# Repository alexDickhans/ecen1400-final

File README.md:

# ECEN 1400 Final Project: Interactive Multi-Game Board System

A physical implementation of multiple board games (Gomoku and Connect 4) using Arduino microcontrollers and servo motors, featuring dual input controllers with haptic feedback and game mode selection.

## 📄 [Project Final Report](/final-report.pdf)

## 🎮 Project Overview

This project creates an interactive 5x5 game board system that supports multiple game modes. Players use physical controllers to place X and O pieces represented by servo motor positions. The system includes haptic feedback, game mode selection, and supports two different input methods (button-based and joystick-based controllers).

## 🏗️ System Architecture

The system consists of three main components:

### 1. Main Board Controller (`main-board/`)
- **Hardware**: Arduino Uno with 2x PCA9685 PWM Servo Driver boards
- **Function**: Controls 25 servo motors arranged in a 5x5 grid
- **Features**: 
  - Multiple game modes (Gomoku 3-5 in a row, Connect 4 3-5 in a row)
  - Game mode selection with visual feedback
  - Game logic and win detection
  - Cursor animation and visual feedback
  - Dual controller communication (separate X and O player controllers)
  - Win sequence animations
  - On-board button controls (SELECT and RESET/START)
  - Movement queue system for optimized servo control

### 2. Coarse Input Controller (`coarse/`)
- **Hardware**: Arduino Uno with 5 digital buttons
- **Function**: Provides directional input via discrete buttons (typically used as one player controller)
- **Features**:
  - Up/Down/Left/Right/Select button inputs
  - Dual UART communication (Hardware Serial + SoftwareSerial)
  - Haptic feedback motor control with multiple patterns

### 3. Fine Input Controller (`fine/`)
- **Hardware**: Arduino Uno with analog joystick
- **Function**: Provides directional input via joystick (typically used as the other player controller)
- **Features**:
  - Analog joystick with threshold detection
  - Dual UART communication (Hardware Serial + SoftwareSerial)
  - Haptic feedback motor control with multiple patterns

## 🔌 Pin Configurations

### Main Board Controller
- **PCA9685 Board 1** (Address 0x40, A0 bridged): Controls servos 0-14
- **PCA9685 Board 2** (Address 0x60, all address pins grounded): Controls servos 15-24
- **X Player Controller**: AltSoftSerial on pins 8/9 (RX/TX)
- **O Player Controller**: SoftwareSerial on pins 5/6 (RX/TX)
- **SELECT Button**: Pin 7 (INPUT_PULLUP)
- **RESET/START Button**: Pin 8 (INPUT_PULLUP) - Note: conflicts with AltSoftSerial, consider different pin

### Coarse Controller
- **Buttons**: 
  - Up: Pin 8
  - Down: Pin 9
  - Left: Pin 10
  - Right: Pin 11
  - Select: Pin 12
- **Haptic Motor**: Pin 13
- **UART**: Hardware Serial (0/1) + SoftwareSerial (4/5 - RX/TX)

### Fine Controller
- **Joystick X**: Pin A0
- **Joystick Y**: Pin A1
- **Select Button**: Pin 3 (INPUT_PULLUP)
- **Haptic Motor**: Pin 13
- **UART**: Hardware Serial (0/1) + SoftwareSerial (6/7 - RX/TX)

## 🎯 Game Features

### Game Modes
The system supports 6 different game modes:

**Gomoku Modes (0-2):**
- Mode 0: 3 in a row (tic-tac-toe style, uses 3x3 sub-board)
- Mode 1: 4 in a row
- Mode 2: 5 in a row (classic Gomoku)

**Connect 4 Modes (3-5):**
- Mode 3: Connect 3
- Mode 4: Connect 4 (classic)
- Mode 5: Connect 5

### Servo States
- **STATE_NONE** (Position 300): Empty space
- **STATE_X** (Position 470): Player X piece
- **STATE_O** (Position 100): Player O piece

### Game Mechanics
- **5x5 Grid**: 25 positions for game pieces
- **Variable Win Condition**: 3-5 pieces in a row depending on selected mode
- **Turn-based**: Players alternate turns (X goes first)
- **Visual Cursor**: Animated cursor shows current selection
  - Gomoku: Full 2D movement (up/down/left/right)
  - Connect 4: Horizontal movement only (left/right) in top row, pieces drop to lowest available position
- **Haptic Feedback**: Controllers vibrate on valid/invalid moves and turn changes
- **Game Mode Selection**: Visual pattern on board shows selected mode before game starts

### Animations
- **Cursor Wiggle**: Visual indication of current position (different patterns for empty vs occupied positions)
- **Checkerboard Pattern**: Idle state animation (alternates every 7 seconds)
- **Game Mode Display**: Visual pattern showing selected game mode (diagonal for Gomoku, bottom row for Connect 4)
- **Connect 4 Drop Animation**: Pieces animate falling from top to target position
- **Win Sequence**: Celebration animation when game is won (expanding wave pattern)

## 📡 Communication Protocol

### Input Commands (Controllers → Main Board)
- `u` - Move cursor up (Gomoku only)
- `d` - Move cursor down (Gomoku only)
- `l` - Move cursor left (or decrease game mode in selection)
- `r` - Move cursor right (or increase game mode in selection)
- `s` - Select/place piece (or start game in selection)
- `x` or `o` - Decrease game mode (in game selection mode)

### Feedback Commands (Main Board → Controllers)
- `y` - Valid move (yes)
- `n` - Invalid move (no)
- `t` - Turn notification (your turn)
- `w` - Game won (win pattern)
- `l` - Game lost (lose pattern)

**Note**: Feedback is sent only to the active player's controller (X or O player receives separate communication)

### Haptic Patterns
- **Yes Pattern** (`y`): Three quick short pulses (...)
- **No Pattern** (`n`): Four long pulses (----)
- **Turn Pattern** (`t`): Long-short-long pulses (-.-)
- **Win Pattern** (`w`): Four dots, two dashes (....--)
- **Lose Pattern** (`l`): Four dashes, two dots (----..)

**Timing**:
- Short pulse: 100ms
- Long pulse: 300ms
- Pause between pulses: 150ms

## 🛠️ Setup Instructions

### Hardware Setup
1. **Main Board**:
   - Connect 2x PCA9685 boards to Arduino Uno via I2C (SDA/SCL)
   - Connect 25 servo motors to PWM outputs
   - First PCA9685: Bridge A0 pin for address 0x40, controls servos 0-14
   - Second PCA9685: Ground all address pins for address 0x60, controls servos 15-24
   - Connect SELECT button to pin 7 (with pull-up)
   - Connect RESET/START button to pin 8 (with pull-up) - Note: may conflict with AltSoftSerial
   - Connect X player controller via AltSoftSerial (pins 8/9)
   - Connect O player controller via SoftwareSerial (pins 5/6)

2. **Controllers**:
   - Connect buttons/joystick as per pin configurations
   - Connect haptic motors to pin 13
   - Connect UART communication lines (both Hardware Serial and SoftwareSerial)

### Software Setup
1. Install required Arduino libraries:
   - `Adafruit PWM Servo Driver Library` (for PCA9685 control)
   - `SoftwareSerial` (built-in, for O player controller)
   - `AltSoftSerial` (for X player controller - more reliable than SoftwareSerial)

2. Upload firmware to each Arduino:
   - `main-board.ino` to main controller
   - `coarse.ino` to button controller (assign to one player)
   - `fine.ino` to joystick controller (assign to other player)

## 🎮 How to Play

1. **Enter Game Selection**: Press SELECT button on main board or 's' on either controller
2. **Select Game Mode**: 
   - Use left/right buttons or l/r commands to cycle through modes (0-5)
   - Board displays visual pattern showing selected mode
   - Gomoku modes (0-2): Diagonal pattern showing pieces in a row
   - Connect 4 modes (3-5): Bottom row pattern showing pieces in a row
3. **Start Game**: Press SELECT button again or 's' command to start
4. **Move Cursor**: 
   - Gomoku: Use up/down/left/right to navigate full board
   - Connect 4: Use left/right to select column (cursor stays in top row)
5. **Place Piece**: Press select to place your piece
   - Connect 4: Piece automatically drops to lowest available position in column
6. **Win**: Get required pieces in a row (3-5 depending on mode) to win
7. **Reset**: Press RESET/START button on main board to return to idle, or game automatically resets after win sequence

## 🔧 Technical Details

### Servo Control
- **Frequency**: 50 Hz PWM
- **Pulse Range**: 90-525 (out of 4096)
- **Actual Positions**: 
  - None: 300 (middle-low)
  - X: 470 (middle-high)
  - O: 100 (low)
- **Movement Queue**: Movements are queued and processed with randomization and staggering to prevent power spikes
- **Concurrent Movements**: Maximum 10 servos can move simultaneously
- **Movement Duration**: 300ms per movement

### Debouncing
- **Button Debounce**: 50ms (main board and controllers)
- **Joystick Debounce**: 100ms
- **Joystick Threshold Values**: 
  - Left: < 400
  - Right: > 600
  - Up: < 400
  - Down: > 600
  - Center: 400-600 (both axes)

### Timing
- **Haptic Pulse**: 100ms duration (short), 300ms (long)
- **Pattern Timing**: 100ms short, 300ms long pulses, 150ms pause between
- **Cursor Animation**: 
  - Empty position: 300ms intervals, ±50 amplitude
  - Occupied position: 150ms intervals, ±25 amplitude
- **Checkerboard Pattern**: Changes every 7 seconds
- **Win Sequence**: 200ms per step, 5 seconds total
- **Connect 4 Drop**: ~200-300ms per row during animation

## 🎯 Game Rules

### Gomoku Modes
- Players alternate turns (X goes first)
- Place pieces on empty positions only
- Win by getting the required pieces in a row (3, 4, or 5 depending on mode)
- Rows can be horizontal, vertical, or diagonal
- Mode 0 (3-in-a-row): Uses 3x3 sub-board (indices 1-3)
- Game ends on win or board full (draw)

### Connect 4 Modes
- Players alternate turns (X goes first)
- Pieces drop to the lowest available position in selected column
- Cannot place in full columns
- Win by getting the required pieces in a row (3, 4, or 5 depending on mode)
- Rows can be horizontal, vertical, or diagonal
- Game ends on win or board full (draw)

## 📁 Project Structure

```
ecen1400-final/
├── README.md              # This file
├── main-board/            # Main game controller
│   └── main-board.ino     # Servo control and game logic
├── coarse/                # Button input controller
│   └── coarse.ino         # Digital button handling
└── fine/                  # Joystick input controller
    └── fine.ino           # Analog joystick handling
```

## 🎓 Educational Value

This project demonstrates:
- **Microcontroller Programming**: Arduino C++ programming with state machines
- **Hardware Integration**: Servo control via I2C, multiple PWM driver boards
- **Game Development**: Multiple game modes, win detection algorithms, turn-based logic
- **User Interface Design**: Haptic feedback, visual feedback, game mode selection
- **Communication Protocols**: Dual UART serial communication (Hardware Serial + SoftwareSerial/AltSoftSerial)
- **System Integration**: Multi-device coordination with separate player controllers
- **Resource Management**: Movement queue system, concurrent movement limiting to prevent power issues
- **Animation Systems**: Cursor animations, win sequences, drop animations

## 🔧 Additional Features

### Simulation Mode
The main board code includes a `SIMULATION_MODE` flag (set to 0 by default) that allows testing game logic without servo hardware. When enabled, board state is printed to serial instead of moving servos.

### Debug Commands (Serial Monitor)
- `start` - Enter game selection mode
- `display` - Show current game state
- `reset` - Reset game to idle state

### State Management
- **IDLE**: Shows checkerboard pattern, waiting for game start
- **GAME_SELECT**: Shows selected game mode pattern, allows mode selection
- **ACTIVE**: Game is running, players can make moves

---

**Course**: ECEN 1400 - Introduction to Digital And Analog Electronics  
**Project**: Interactive Multi-Game Board System  
**Technologies**: Arduino, C++, Servo Motors, Haptic Feedback, I2C, UART Communication

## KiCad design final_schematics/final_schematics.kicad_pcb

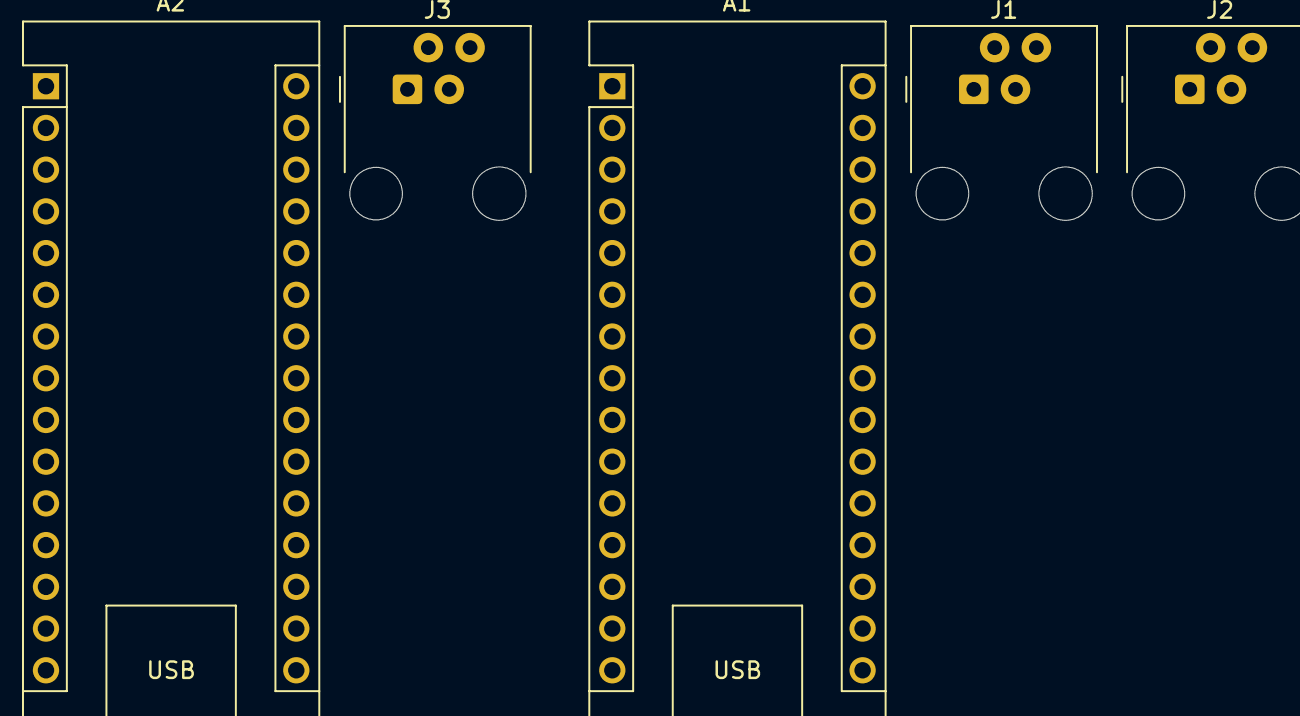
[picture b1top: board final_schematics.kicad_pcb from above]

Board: 2 copper layers, 5 parts (0 on the bottom side), 6 nets, no tracks yet.

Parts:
A1, A2: Arduino_Nano_v3.x; Arduino_Nano
J1, J2: Input device 1; RJ9_Evercom_5301-440xxx_Horizontal
J3: RJ9; RJ9_Evercom_5301-440xxx_Horizontal

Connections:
+5V: A2.30 (VIN), J1.4, J2.4, J3.4
/Coarse Motor Control/RX: A1.8 (D5), A2.8 (D5), J1.2, J3.2
/Coarse Motor Control/TX: A1.7 (D4), A2.7 (D4), J1.3, J3.3
/Main Board/RX2: A1.9 (D6), J2.3
/Main Board/TX2: A1.10 (D7), J2.2
GND: A2.4 (GND), A2.29 (GND), J1.1, J2.1, J3.1

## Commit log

2025-10-03 Add basic coarse control code
2025-10-03 finalize haptic code
2025-10-03 Initial main board code made with cursor
2025-10-03 Finalize inputs
2025-10-06 Add readme
2025-10-10 Adding final schematic models
2025-10-10 Fix debounce logic
2025-10-14 Update resume
2025-10-17 Test code on main board
2025-10-27 Add testing code
2025-10-27 Getting ready for testing in sim with main board
2025-10-27 Almost ready to play a full game
2025-10-28 game working without haptics
2025-10-31 Functional demo ready
2025-11-04 Fix servos getting stuck in the wrong posision
2025-11-04 Main board code basically done'
2025-11-04 Fix weird haptics bugs
2025-11-04 Code ready for expo
2025-11-04 Connect 4 looking good
2025-11-05 Add full game board condition
2025-11-13 change indicies to the real board
2025-11-14 Restore proper ordering
2025-11-14 Add queue fixes so it can't get stuck in weird modes
2025-11-15 Tested
2025-12-02 Add flowcharts
2025-12-02 Add link for final report
2025-12-05 upload final report
